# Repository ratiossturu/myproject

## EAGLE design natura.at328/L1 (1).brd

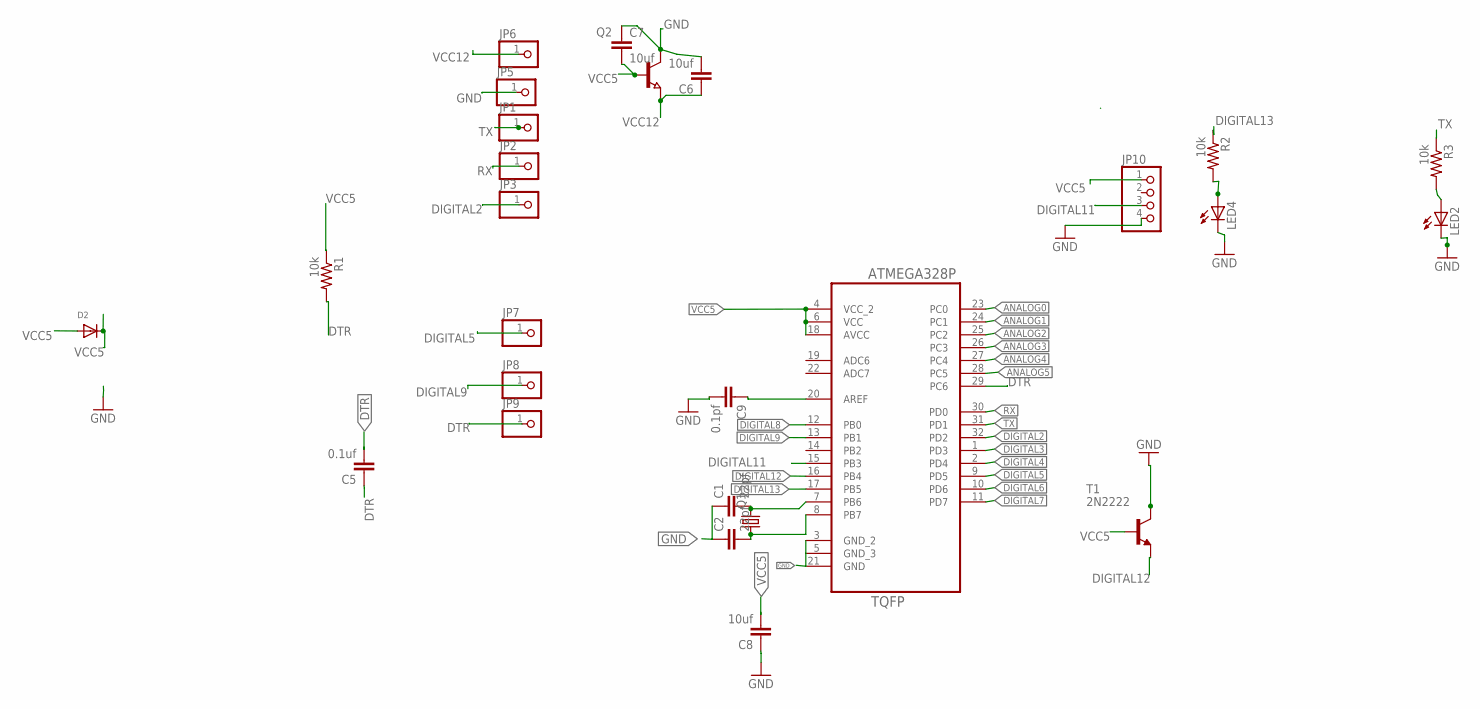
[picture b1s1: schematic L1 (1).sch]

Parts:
C1, C2: 22pf; C0603
C5: 0.1uf; C0805
C6, C7, C8: 10uf; C0805
C9: 0.1pf; C0805
D2: DIODESMA; SMADIODE
JP1, JP2, JP3, JP5, JP6, JP7, JP8, JP9: PINHD-1X1; 1X01
JP10: PINHD-1X4; 1X04
LED2, LED4: LEDCHIPLED_0805; CHIPLED_0805
Q1: CRYSTALTC26V; TC26V
Q2: NPN-TRANSISTOR_SOT23; SOT23
R1, R2, R3: 10k; R0603
T1: 2N2222; TO92-EBC-OVAL
U2: ATMEGA328P-AU; QFP80P900X900X120-32N

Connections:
ANALOG0: U2.23 (PC0)
ANALOG1: U2.24 (PC1)
ANALOG2: U2.25 (PC2)
ANALOG3: U2.26 (PC3)
ANALOG4: U2.27 (PC4)
ANALOG5: U2.28 (PC5)
DIGITAL2: JP3.1, U2.32 (PD2)
DIGITAL3: U2.1 (PD3)
DIGITAL4: U2.2 (PD4)
DIGITAL5: JP7.1, U2.9 (PD5)
DIGITAL6: U2.10 (PD6)
DIGITAL7: U2.11 (PD7)
DIGITAL8: U2.12 (PB0)
DIGITAL9: JP8.1, U2.13 (PB1)
DIGITAL11: JP10.3, U2.15 (PB3)
DIGITAL12: T1.E, U2.16 (PB4)
DIGITAL13: R2.1, U2.17 (PB5)
DTR: C5.1, C5.2, JP9.1, R1.2, U2.29 (PC6)
GND: C1.1, C2.1, C6.2, C7.1, C8.1, C9.2, JP5.1, JP10.4, LED2.C, LED4.C, Q2.3 (C), T1.C, U2.3 (GND_2), U2.5 (GND_3), U2.21 (GND)
unnamed: LED2.A, R3.2
unnamed: C1.2, Q1.2, U2.7 (PB6)
unnamed: C2.2, Q1.1, U2.8 (PB7)
unnamed: C9.1, U2.20 (AREF)
unnamed: LED4.A, R2.2
RX: JP2.1, U2.30 (PD0)
TX: JP1.1, R3.1, U2.31 (PD1)
VCC5: C7.2, C8.2, D2.A, D2.C, JP10.1, Q2.1 (B), R1.1, T1.B, U2.4 (VCC_2), U2.6 (VCC), U2.18 (AVCC)
VCC12: C6.1, JP6.1, Q2.2 (E)

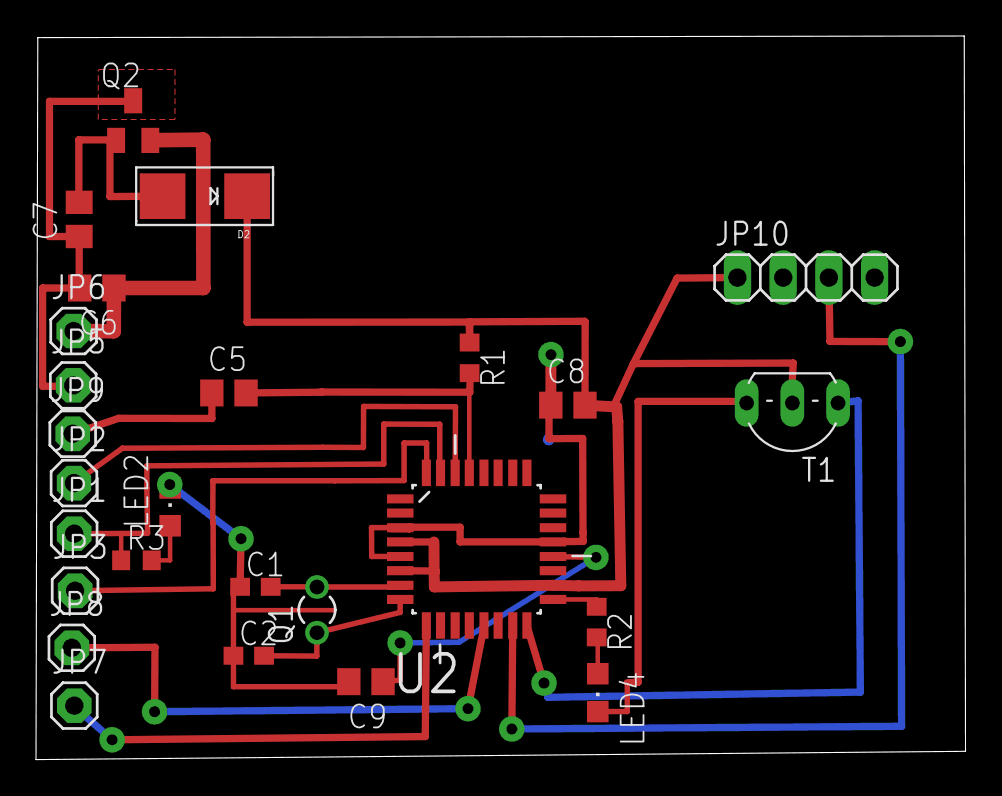
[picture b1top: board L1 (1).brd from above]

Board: 2 copper layers, 51.6 x 40.2 mm, 26 parts (0 on the bottom side), 17 nets.

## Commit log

2016-09-29 ragaca
